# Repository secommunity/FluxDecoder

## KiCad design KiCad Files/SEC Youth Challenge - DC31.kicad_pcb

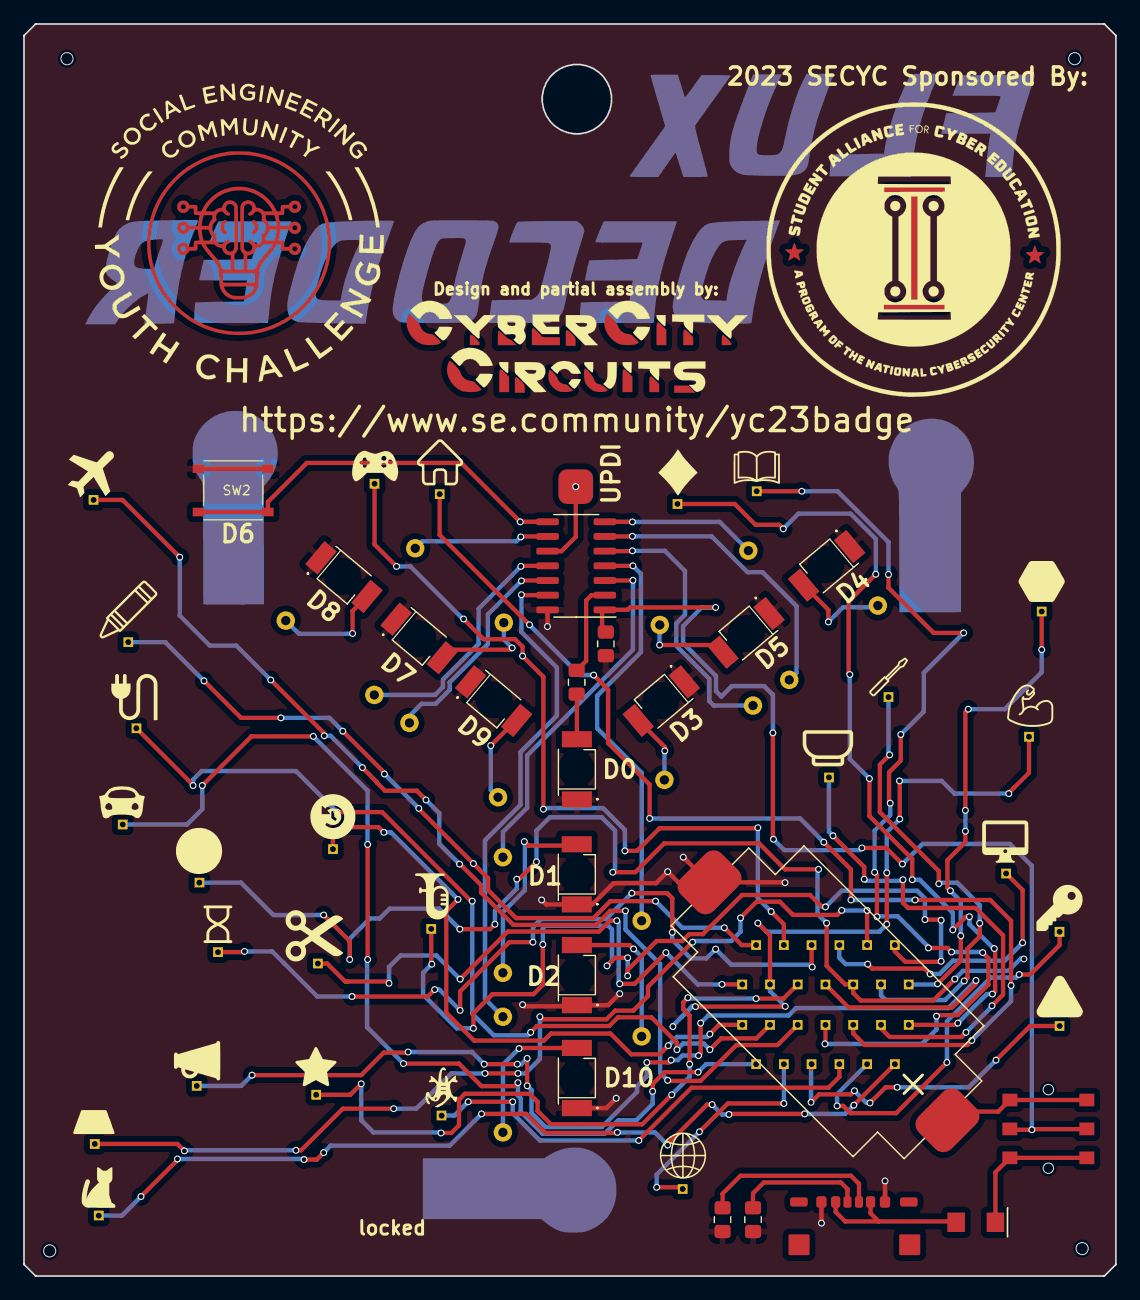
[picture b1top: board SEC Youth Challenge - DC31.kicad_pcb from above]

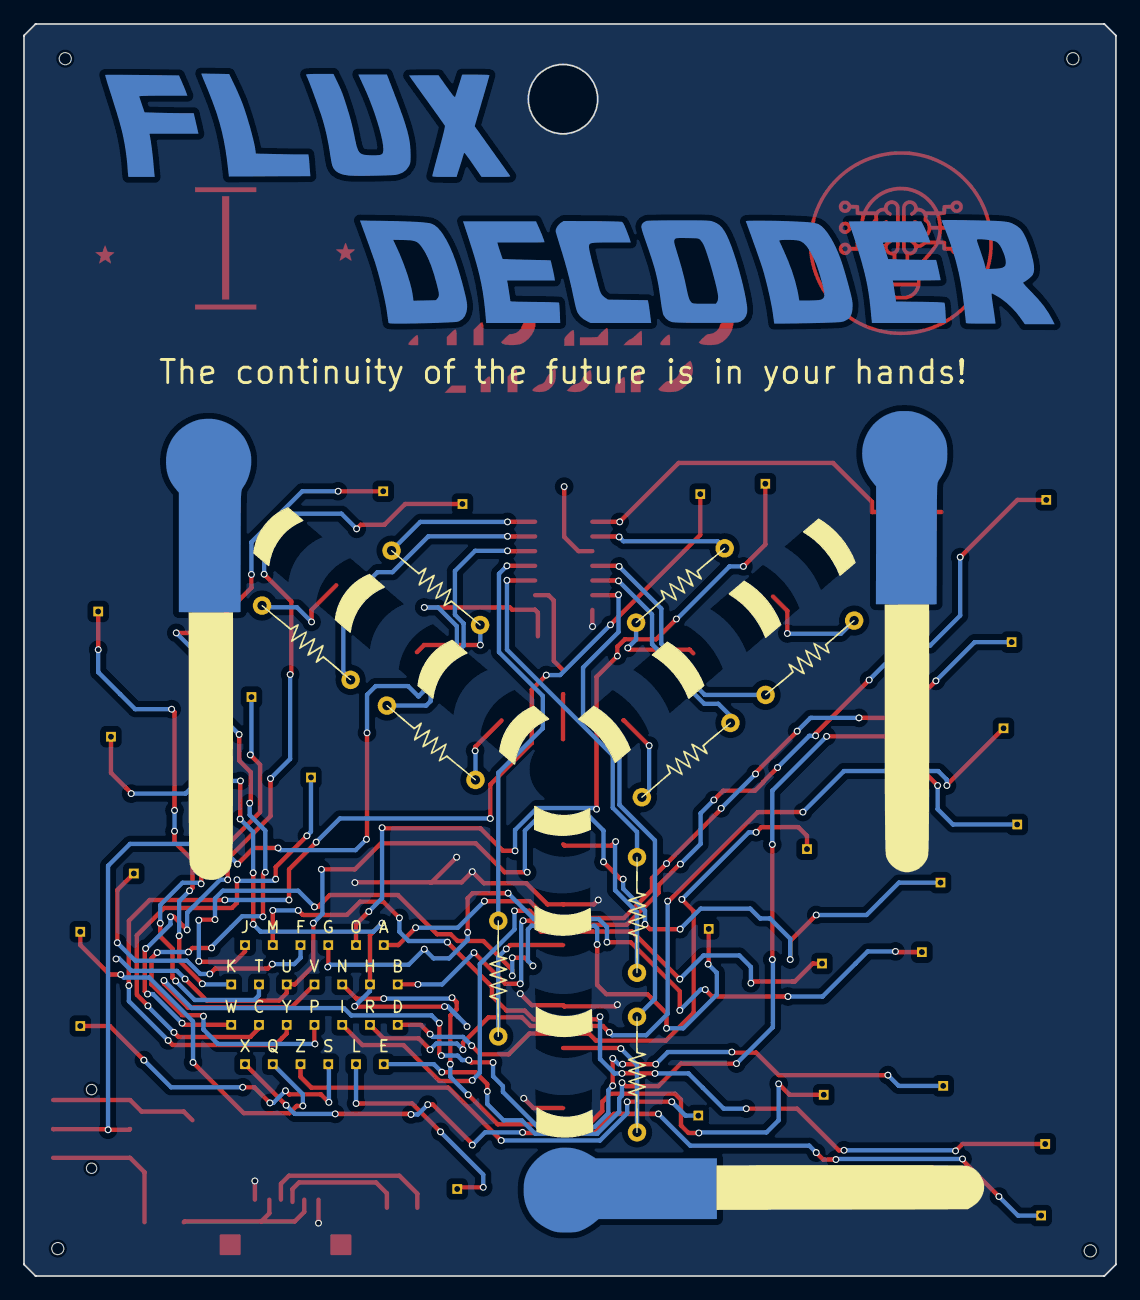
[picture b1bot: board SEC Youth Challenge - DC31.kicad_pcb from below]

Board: 2 copper layers, 94.4 x 108.3 mm, 82 parts (35 on the bottom side), 55 nets.

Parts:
A: TestPoint; PinHeader_1x01_P1.00mm_Vertical
AL1, AL2, AL3, AL4, AL5, AL6, AL7, AL8, AL9, AL10, AL11, AL12, AL13, AL14, AL15, AL16, AL17, AL18, AL19, AL20, AL21, AL22, AL23, AL24, AL25, AL26: TestPoint; PinHeader_1x01_P1.00mm_Vertical
B: TestPoint; PinHeader_1x01_P1.00mm_Vertical
BT1: Battery_Cell; CR2032-LCSC-C964760
C: TestPoint; PinHeader_1x01_P1.00mm_Vertical
C1: 0.1uF; C_0805
D: TestPoint; PinHeader_1x01_P1.00mm_Vertical
D1, D2, D3, D4, D5, D6, D7, D8, D9, D10: LED; LED_PLCC-2_REVMNT_3.2x2.8mm
D11: Schottky; DO-214AC
E: TestPoint; PinHeader_1x01_P1.00mm_Vertical
F: TestPoint; PinHeader_1x01_P1.00mm_Vertical
G: TestPoint; PinHeader_1x01_P1.00mm_Vertical
H: TestPoint; PinHeader_1x01_P1.00mm_Vertical
I: TestPoint; PinHeader_1x01_P1.00mm_Vertical
J: TestPoint; PinHeader_1x01_P1.00mm_Vertical
J1: USB_C_Power_Only_C2927027; USB C Power Only C2927027
J2: UDPI PROGRAMMING PAD; UDPI PAD
K: TestPoint; PinHeader_1x01_P1.00mm_Vertical
L: TestPoint; PinHeader_1x01_P1.00mm_Vertical
M: TestPoint; PinHeader_1x01_P1.00mm_Vertical
N: TestPoint; PinHeader_1x01_P1.00mm_Vertical
O: TestPoint; PinHeader_1x01_P1.00mm_Vertical
P: TestPoint; PinHeader_1x01_P1.00mm_Vertical
Q: TestPoint; PinHeader_1x01_P1.00mm_Vertical
R: TestPoint; PinHeader_1x01_P1.00mm_Vertical
R1, R2, R3, R4, R5, R6, R7, R8, R9: R_LED; Schematic - Resistor 10.00mm
R10: R_LED; R_0805_NoText
R11, R12: 5.1 kΩ; R_0805
S: TestPoint; PinHeader_1x01_P1.00mm_Vertical
SW1: SW_SPDT; Switch, Side - LCSC C963207
SW2: SW_Push; 500-0001-TS1187ACGB-(2_Pin)
T: TestPoint; PinHeader_1x01_P1.00mm_Vertical
U: TestPoint; PinHeader_1x01_P1.00mm_Vertical
U1: ATtiny1614-SS; SOIC-14_3.9x8.7mm_P1.27mm
V: TestPoint; PinHeader_1x01_P1.00mm_Vertical
W: TestPoint; PinHeader_1x01_P1.00mm_Vertical
X: TestPoint; PinHeader_1x01_P1.00mm_Vertical
Y: TestPoint; PinHeader_1x01_P1.00mm_Vertical
Z: TestPoint; PinHeader_1x01_P1.00mm_Vertical

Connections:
+5V: D11.1 (K), SW1.1 (A)
+BATT: BT1.1 (+), SW1.3 (C)
/D00: R10.1, U1.2 (PA4)
/D01: R4.1, U1.3 (PA5)
/D02: R5.1, U1.4 (PA6)
/D03: R1.1, U1.5 (PA7)
/D04: R3.1, U1.6 (PB3)
/D05: R2.1, U1.7 (PB2)
/D06: SW2.1, U1.8 (PB1)
/D07: R8.1, U1.9 (PB0)
/D08: R9.1, U1.11 (PA1)
/D09: R7.1, U1.12 (PA2)
/D10: R6.1, U1.13 (PA3)
/SYM_A: A.1, AL1.1
/SYM_B: AL2.1, B.1
/SYM_C: AL3.1, C.1
/SYM_D: AL4.1, D.1
/SYM_E: AL5.1, E.1
/SYM_F: AL6.1, F.1
/SYM_G: AL7.1, G.1
/SYM_H: AL8.1, H.1
/SYM_I: AL9.1, I.1
/SYM_J: AL10.1, J.1
/SYM_K: AL11.1, K.1
/SYM_L: AL12.1, L.1
/SYM_M: AL13.1, M.1
/SYM_N: AL14.1, N.1
/SYM_O: AL15.1, O.1
/SYM_P: AL16.1, P.1
/SYM_Q: AL17.1, Q.1
/SYM_R: AL18.1, R.1
/SYM_S: AL19.1, S.1
/SYM_T: AL20.1, T.1
/SYM_U: AL21.1, U.1
/SYM_V: AL22.1, V.1
/SYM_W: AL23.1, W.1
/SYM_X: AL24.1, X.1
/SYM_Y: AL25.1, Y.1
/SYM_Z: AL26.1, Z.1
/UDPI: J2.1, U1.10 (~RESET/PA0)
GND: BT1.2 (-), C1.1, D1.1 (K), D2.1 (K), D3.1 (K), D4.1 (K), D5.1 (K), D6.1 (K), D7.1 (K), D8.1 (K), D9.1 (K), D10.1 (K), J1.A1 (GND), R11.1, R12.1, SW2.2, U1.14 (GND)
unnamed: D1.2 (A), R1.2
unnamed: D2.2 (A), R2.2
unnamed: D3.2 (A), R3.2
unnamed: D4.2 (A), R4.2
unnamed: D5.2 (A), R5.2
unnamed: D6.2 (A), R6.2
unnamed: D7.2 (A), R7.2
unnamed: D8.2 (A), R8.2
unnamed: D9.2 (A), R9.2
unnamed: D10.2 (A), R10.2
unnamed: D11.2 (A), J1.A4 (VBUS), J1.B4 (VBUS)
unnamed: J1.A5 (CC1), R11.2
unnamed: J1.B5 (CC2), R12.2
VCC: C1.2, SW1.2 (B), U1.1 (VCC)

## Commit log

2023-08-10 Code and Schematics
2023-08-10 added readme
2023-08-10 oops
